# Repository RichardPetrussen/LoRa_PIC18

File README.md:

# LoRa_PIC18
Small LoRa Board with an PIC18 MCU

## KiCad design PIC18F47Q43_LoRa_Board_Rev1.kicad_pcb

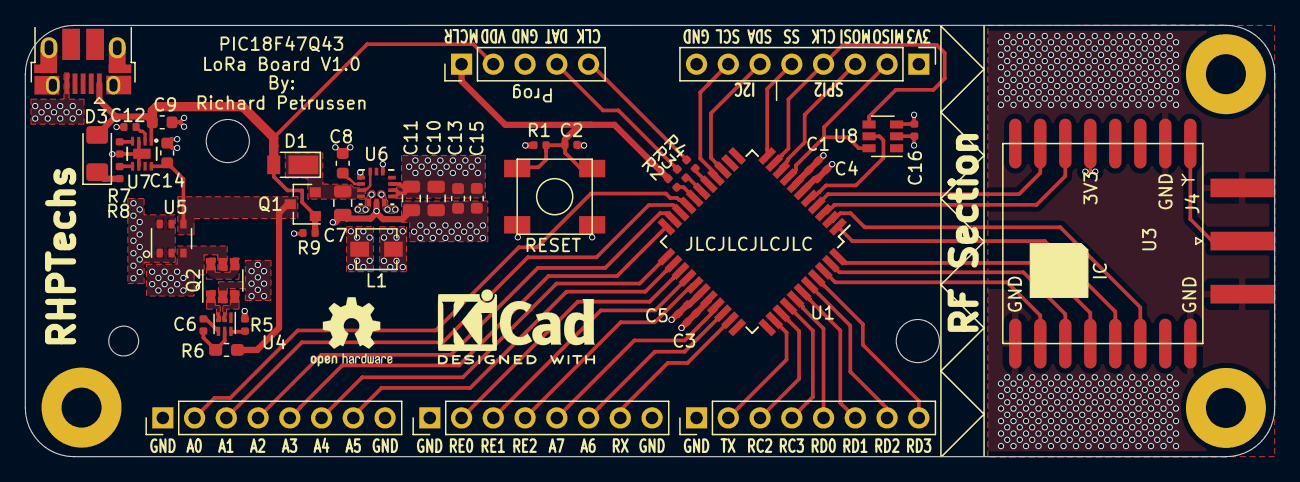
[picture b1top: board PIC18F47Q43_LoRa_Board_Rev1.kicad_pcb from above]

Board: 4 copper layers, 100.0 x 34.5 mm, 49 parts (1 on the bottom side), 59 nets.

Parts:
BT1: Battery_Cell; BatteryHolder_Keystone_1042_1x18650
C1, C2, C3, C6, C16: 100nF; C_0402_1005Metric
C4, C5: 10nF; C_0402_1005Metric
C7, C10, C11: 10uF; C_0805_2012Metric
C8, C9, C13, C14, C15: 1uF; C_0603_1608Metric
C12: 470nF; C_0402_1005Metric
D1: DFLS120L-7; D_PowerDI-123
D3: RED; LED_1206_3216Metric_Pad1.42x1.75mm_HandSolder
H2, H3, H4: MountingHole_Pad; MountingHole_3.2mm_M3_Pad
J1: Prog; PinHeader_1x05_P2.54mm_Vertical
J2: Analog; PinHeader_1x08_P2.54mm_Vertical
J3: COM; PinHeader_1x08_P2.54mm_Vertical
J4: SMA; SMA_Amphenol_132289_EdgeMount
J5: USB_B_Micro; USB_Micro-B_Amphenol_10103594-0001LF_Horizontal
J6, J7: MISC; PinHeader_1x08_P2.54mm_Vertical
L1: 1uH; L_Vishay_IHLP-1212
Q1: DMB2045UQ; SOT-23
Q2: FDC6305N; SuperSOT-6
R1, R9: 10k; R_0402_1005Metric
R2: 470R; R_0402_1005Metric
R3, R4: 49R9; R_0402_1005Metric
R5: 2200; R_0402_1005Metric
R6: 330R; R_0603_1608Metric_Pad1.05x0.95mm_HandSolder
R7: 2R8k; R_0402_1005Metric
R8: 510R; R_0402_1005Metric
SW1: RESET; Push_Button_4_Term
U1: PIC18L47Q43; TQFP-44_10x10mm_P0.8mm
U3: RF96
U4: BQ29700; WSON-6_1.5x1.5mm_P0.5mm
U5: Si3493BDV; TSOP-6_1.65x3.05mm_P0.95mm
U6: MAX77827AEFD+T; MAX77827AEFD&plus_T
U7: max8808xeta+; max8808xeta&plus_
U8: TMP121; SOT-23-6

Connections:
!MCLR: C2.1, J1.1, R1.1, R2.1, SW1.3, SW1.4
+3V3: C1.1, C3.1, C4.1, C5.1, C10.1, C11.1, C13.1, C15.1, C16.2, J3.1, R1.2, U1.7, U1.28, U3.13, U6.11, U6.12, U6.13, U8.3
+BATT: C14.1, Q1.3, R6.1, U5.4, U7.8
ANA0: J2.2, U1.19
ANA1: J2.3, U1.20
ANA2: J2.4, U1.21
ANA3: J2.5, U1.22
ANA4: J2.6, U1.23
ANA5: J2.7, U1.24
ANA6: J6.6, U1.31
ANA7: J6.5, U1.30
GND: C1.2, C2.2, C3.2, C4.2, C5.2, C7.2, C8.2, C9.2, C10.2, C11.2, C12.2, C13.2, C14.2, C15.2, C16.1, H2.1, J1.3, J2.1, J2.8, J3.8, J4.2, J5.5, J6.1, J6.8, J7.1, Q2.2, R5.2, R7.1, R9.1, SW1.1, SW1.2, U1.6, U1.29, U3.1, U3.8, U3.10, U6.1, U6.4, U6.9, U7.3, U7.6, U7.9, U8.2
I2C_SCL: J3.7, U1.15
I2C_SDA: J3.6, U1.14
ICSPCLK: J1.5, R4.2
ICSPDAT: J1.4, R3.2
LoRa_DIO0: U1.3, U3.14
LoRa_DIO1: U1.4, U3.15
LoRa_RESET: U1.2, U3.6
unnamed: BT1.1, U5.1, U5.2, U5.5, U5.6
unnamed: BT1.2, C6.2, Q2.5, U4.4, U5.3
unnamed: C6.1, R6.2, U4.5
unnamed: C7.1, D1.1, Q1.2, U6.3, U6.6, U6.7
unnamed: C8.1, U6.5
unnamed: C12.1, U7.2
unnamed: D3.1, R8.2
unnamed: J4.1, U3.9
unnamed: L1.1, U6.10
unnamed: L1.2, U6.8
unnamed: Q2.1, U4.3
unnamed: Q2.3, U4.2
unnamed: Q2.4, Q2.6
unnamed: R2.2, U1.18
unnamed: R3.1, U1.17
unnamed: R4.1, U1.16
unnamed: R5.1, U4.6
unnamed: R7.2, U7.4
unnamed: R8.1, U7.5
RC2: J7.3, U1.36
RC3: J7.4, U1.37
RD0: J7.5, U1.38
RD1: J7.6, U1.39
RD2: J7.7, U1.40
RD3: J7.8, U1.41
RE0: J6.2, U1.25
RE1: J6.3, U1.26
RE2: J6.4, U1.27
SPI1_CLK: U1.44, U3.4
SPI1_MISO: U1.42, U3.2
SPI1_MOSI: U1.43, U3.3
SPI1_SS_LoRa: U1.1, U3.5
SPI2_CLK: J3.4, U1.10, U8.4
SPI2_MISO: J3.2, U1.8, U8.6
SPI2_MOSI: J3.3, U1.9
SPI2_SS: J3.5, U1.11
TEMP_SS: U1.5, U8.5
UART1_RX: J6.7, U1.32
UART1_TX: J7.2, U1.35
VDD: C9.1, D1.2, D3.2, J1.2, J5.1, Q1.1, R9.2, U7.1

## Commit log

2021-03-16 Inital Commit
